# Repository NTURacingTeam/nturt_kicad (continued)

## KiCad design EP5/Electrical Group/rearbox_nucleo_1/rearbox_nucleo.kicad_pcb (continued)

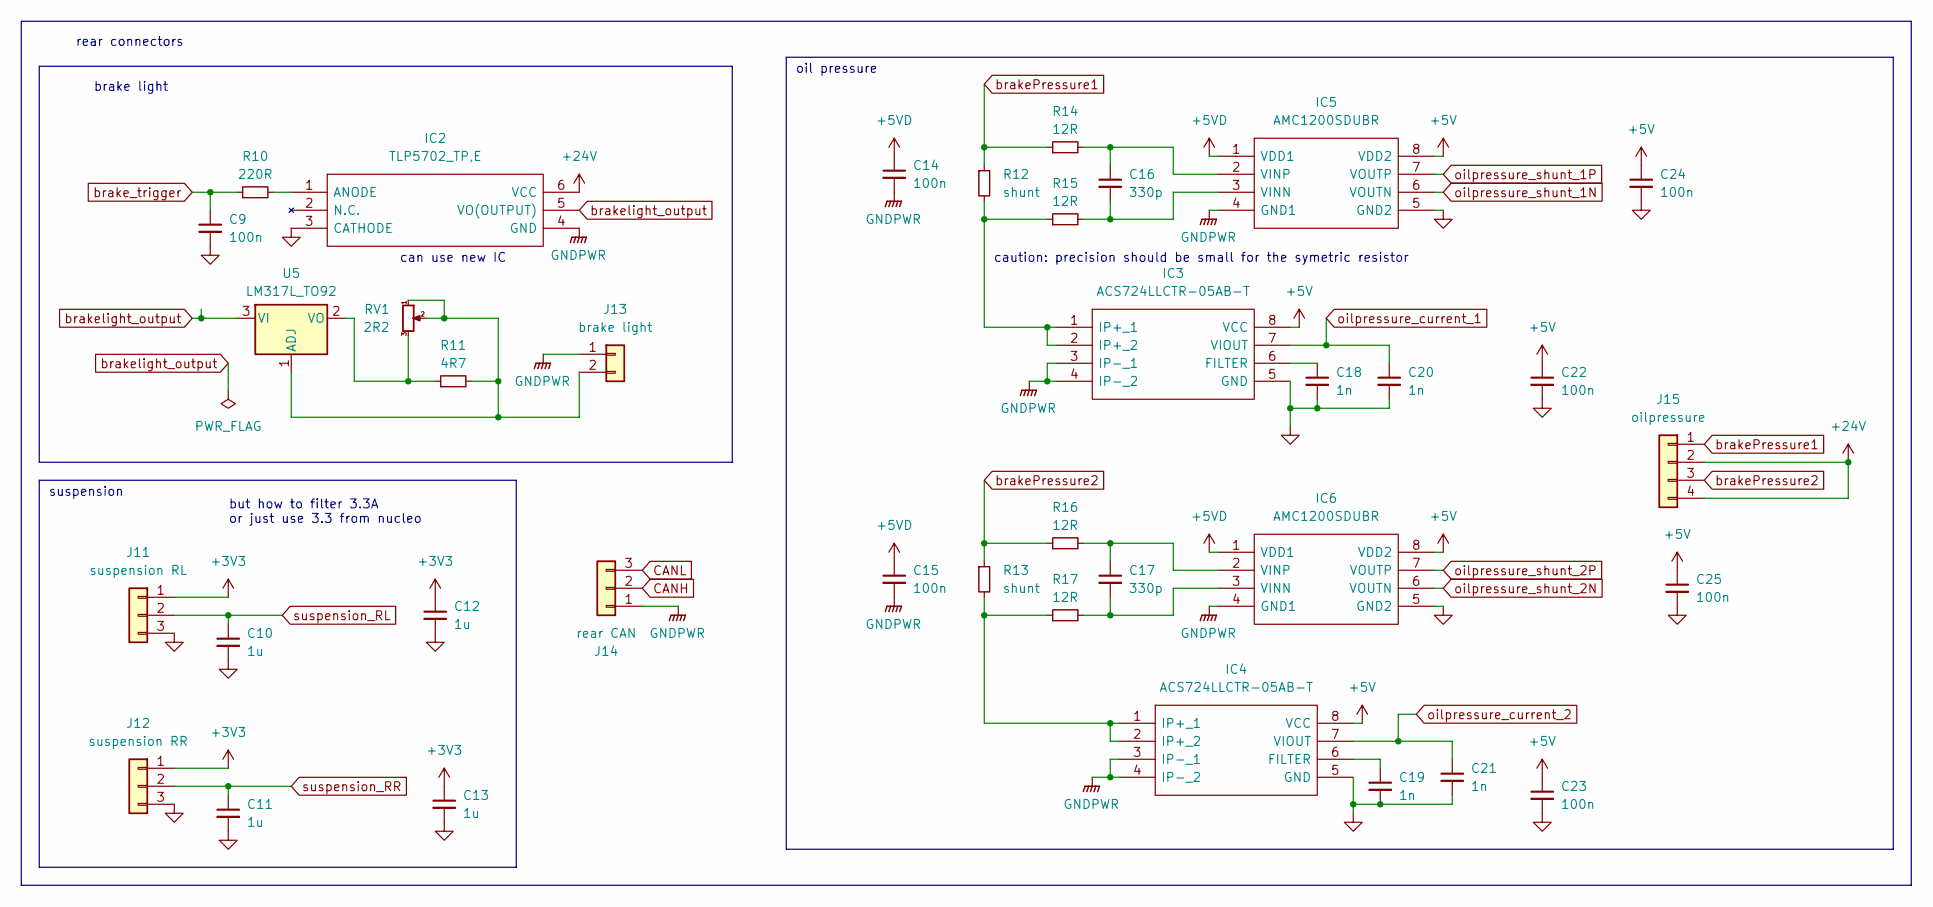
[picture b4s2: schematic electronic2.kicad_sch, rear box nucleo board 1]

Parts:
C9, C14, C15, C22, C23, C24, C25: 100n; C_0805_2012Metric
C10, C11, C12, C13: 1u; C_0805_2012Metric
C16, C17: 330p; C_0805_2012Metric
C18, C19, C20, C21: 1n; C_0805_2012Metric
IC2: TLP5702_TP,E; SOT127P1000X230-6N; Mouser Part Number 757-TLP5702(TPE
IC3, IC4: ACS724LLCTR-05AB-T; SOIC127P600X175-8N; Mouser Part Number 250-724LLCTR05ABT
IC5, IC6: AMC1200SDUBR; SOP254P1040X485-8N; Mouser Part Number 595-AMC1200SDUBR
J11: suspension RL; JST_XH_B3B-XH-A_1x03_P2.50mm_Vertical
J12: suspension RR; JST_XH_B3B-XH-A_1x03_P2.50mm_Vertical
J13: brake light; JST_XH_B2B-XH-A_1x02_P2.50mm_Vertical
J14: rear CAN; JST_XH_B3B-XH-A_1x03_P2.50mm_Vertical
J15: oilpressure; JST_XH_B4B-XH-A_1x04_P2.50mm_Vertical
R10: 220R; R_0805_2012Metric
R11: 4R7; R_Axial_DIN0516_L15.5mm_D5.0mm_P5.08mm_Vertical
R12, R13: shunt; R_0805_2012Metric
R14, R15, R16, R17: 12R; R_0805_2012Metric
RV1: 2R2; Potentiometer_Piher_T-16H_Single_Horizontal
U5: LM317L_TO92; TO-220-3_Vertical

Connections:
+3V3: C12.1, C13.1, J11.1, J12.1; also elsewhere on the board
+5V: C22.1, C23.1, C24.1, C25.1, IC3.8 (VCC), IC4.8 (VCC), IC5.8 (VDD2), IC6.8 (VDD2); also elsewhere on the board
+5VD: C14.1, C15.1, IC5.1 (VDD1), IC6.1 (VDD1); also elsewhere on the board
CANH: J14.2; also elsewhere on the board
CANL: J14.3; also elsewhere on the board
GND: C9.2, C10.2, C11.2, C12.2, C13.2, C18.2, C19.2, C20.2, C21.2, C22.2, C23.2, C24.2, C25.2, IC2.3 (CATHODE), IC3.5 (GND), IC4.5 (GND), IC5.5 (GND2), IC6.5 (GND2), J11.3, J12.3; also elsewhere on the board
GNDPWR: C14.2, C15.2, IC2.4 (GND), IC3.3 (IP-_1), IC3.4 (IP-_2), IC4.3 (IP-_1), IC4.4 (IP-_2), IC5.4 (GND1), IC6.4 (GND1), J13.1, J14.1; also elsewhere on the board
unnamed: IC2.1 (ANODE), R10.2
unnamed: C18.1, IC3.6 (FILTER)
unnamed: IC3.1 (IP+_1), IC3.2 (IP+_2), R12.2, R15.1
unnamed: C19.1, IC4.6 (FILTER)
unnamed: IC4.1 (IP+_1), IC4.2 (IP+_2), R13.2, R17.1
unnamed: C16.2, IC5.3 (VINN), R15.2
unnamed: C16.1, IC5.2 (VINP), R14.2
unnamed: C17.2, IC6.3 (VINN), R17.2
unnamed: C17.1, IC6.2 (VINP), R16.2
unnamed: J13.2, R11.2, RV1.1, RV1.2, U5.1 (ADJ)
unnamed: R11.1, RV1.3, U5.2 (VO)
brakePressure1: J15.1, R12.1, R14.1
brakePressure2: J15.3, R13.1, R16.1
brake_trigger: C9.1, R10.1; also elsewhere on the board
brakelight_output: IC2.5 (VO(OUTPUT)), U5.3 (VI)
oilpressure_current_1: C20.1, IC3.7 (VIOUT); also elsewhere on the board
oilpressure_current_2: C21.1, IC4.7 (VIOUT); also elsewhere on the board
oilpressure_shunt_1N: IC5.6 (VOUTN); also elsewhere on the board
oilpressure_shunt_1P: IC5.7 (VOUTP); also elsewhere on the board
oilpressure_shunt_2N: IC6.6 (VOUTN); also elsewhere on the board
oilpressure_shunt_2P: IC6.7 (VOUTP); also elsewhere on the board
suspension_RL: C10.1, J11.2; also elsewhere on the board
suspension_RR: C11.1, J12.2; also elsewhere on the board

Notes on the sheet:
can use new IC
oil pressure
but how to filter 3.3A or just use 3.3 from nucleo
caution: precision should be small for the symetric resistor
brake light
rear connectors
suspension

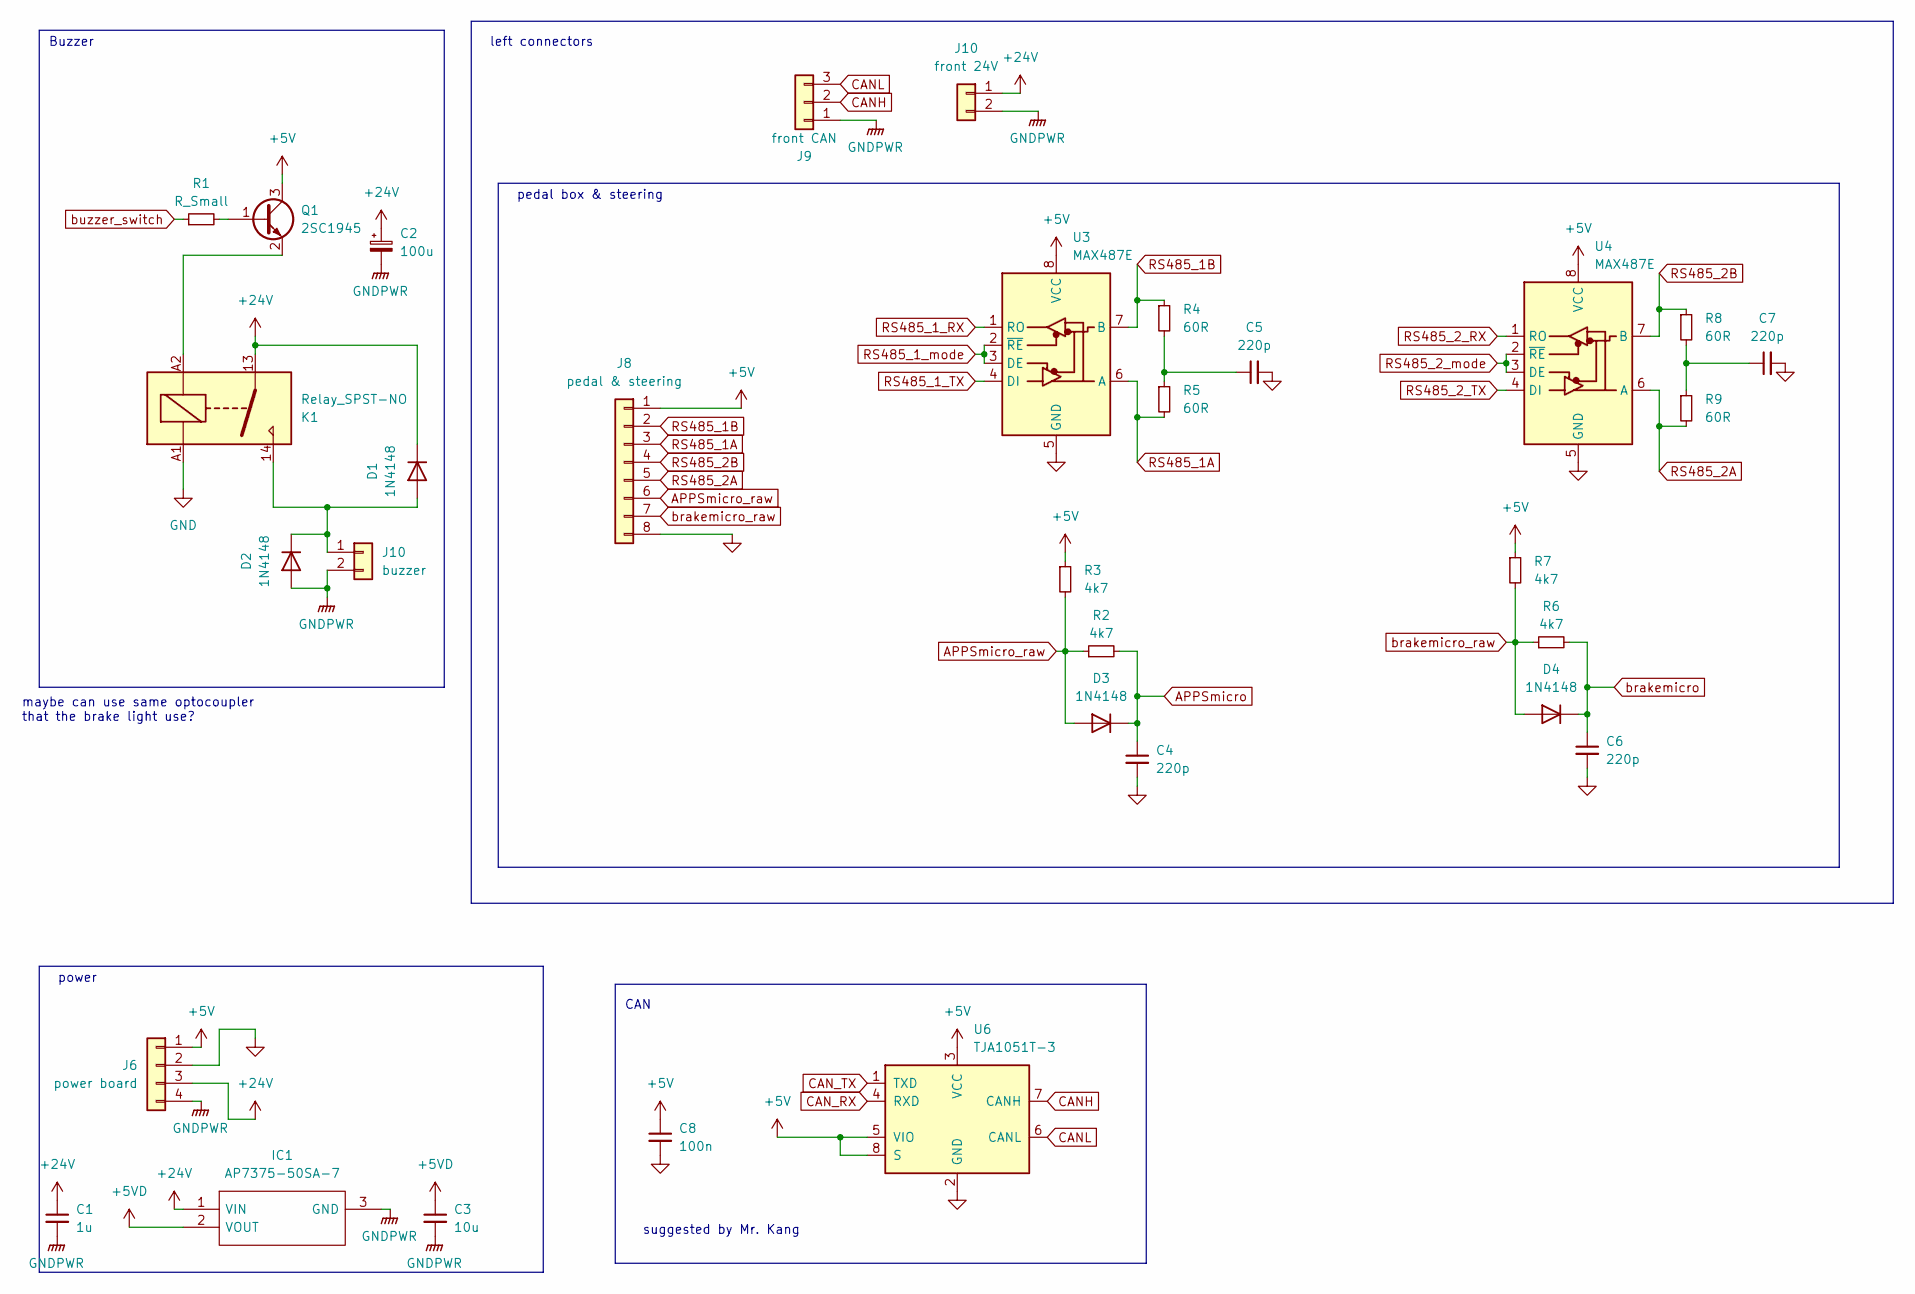
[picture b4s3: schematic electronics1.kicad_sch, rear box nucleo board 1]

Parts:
C1: 1u; C_0805_2012Metric
C2: 100u; C_Radial_D6.3mm_H11.0mm_P2.50mm
C3: 10u; C_0805_2012Metric
C4, C5, C6, C7: 220p; C_0805_2012Metric
C8: 100n; C_0805_2012Metric
D1, D2, D3, D4: 1N4148; D_MiniMELF
IC1: AP7375-50SA-7; SOT96P240X110-3N; Mouser Part Number 621-AP7375-50SA-7
J6: power board; JST_XH_B4B-XH-A_1x04_P2.50mm_Vertical
J8: pedal & steering; JST_XH_B8B-XH-A_1x08_P2.50mm_Vertical
J9: front CAN; JST_XH_B3B-XH-A_1x03_P2.50mm_Vertical
J10: buzzer; JST_XH_B2B-XH-A_1x02_P2.50mm_Vertical
K1: Relay_SPST-NO; Relay_SPST_Omron_G2RL-1A-E
Q1: 2SC1945; TO-220-3_Vertical
R1: R_Small; R_0805_2012Metric
R2, R3, R6, R7: 4k7; R_0805_2012Metric
R4, R5, R8, R9: 60R; R_0805_2012Metric
U3, U4: MAX487E; SOIC-8_3.9x4.9mm_P1.27mm
U6: TJA1051T-3; SOIC-8_3.9x4.9mm_P1.27mm

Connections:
+5V: C8.1, J6.1, J8.1, Q1.3 (C), R3.1, R7.1, U3.8 (VCC), U4.8 (VCC); also elsewhere on the board
+5VD: C3.1, IC1.2 (VOUT); also elsewhere on the board
APPSmicro: C4.1, D3.1 (K), R2.2; also elsewhere on the board
APPSmicro_raw: D3.2 (A), J8.6, R2.1, R3.2
CANH: J9.2; also elsewhere on the board
CANL: J9.3; also elsewhere on the board
GND: C4.2, C5.2, C6.2, C7.2, C8.2, J6.2, J8.8, K1.A1, U3.5 (GND), U4.5 (GND); also elsewhere on the board
GNDPWR: C1.2, C2.2, C3.2, D2.2 (A), IC1.3 (GND), J6.4, J9.1, J10.2; also elsewhere on the board
unnamed: C5.1, R4.2, R5.1
unnamed: C7.1, R8.2, R9.1
unnamed: Q1.1 (B), R1.2
unnamed: K1.A2, Q1.2 (E)
RS485_1A: J8.3, R5.2, U3.6 (A)
RS485_1B: J8.2, R4.1, U3.7 (B)
RS485_1_RX: U3.1 (RO); also elsewhere on the board
RS485_1_TX: U3.4 (DI); also elsewhere on the board
RS485_1_mode: U3.2 (~RE), U3.3 (DE); also elsewhere on the board
RS485_2A: J8.5, R9.2, U4.6 (A)
RS485_2B: J8.4, R8.1, U4.7 (B)
RS485_2_RX: U4.1 (RO); also elsewhere on the board
RS485_2_TX: U4.4 (DI); also elsewhere on the board
RS485_2_mode: U4.2 (~RE), U4.3 (DE); also elsewhere on the board
brakemicro: C6.1, D4.1 (K), R6.2; also elsewhere on the board
brakemicro_raw: D4.2 (A), J8.7, R6.1, R7.2
buzzer_switch: R1.1; also elsewhere on the board

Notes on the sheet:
Buzzer
maybe can use same optocoupler that the brake light use?
power
pedal box & steering
suggested by Mr. Kang
CAN
left connectors

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
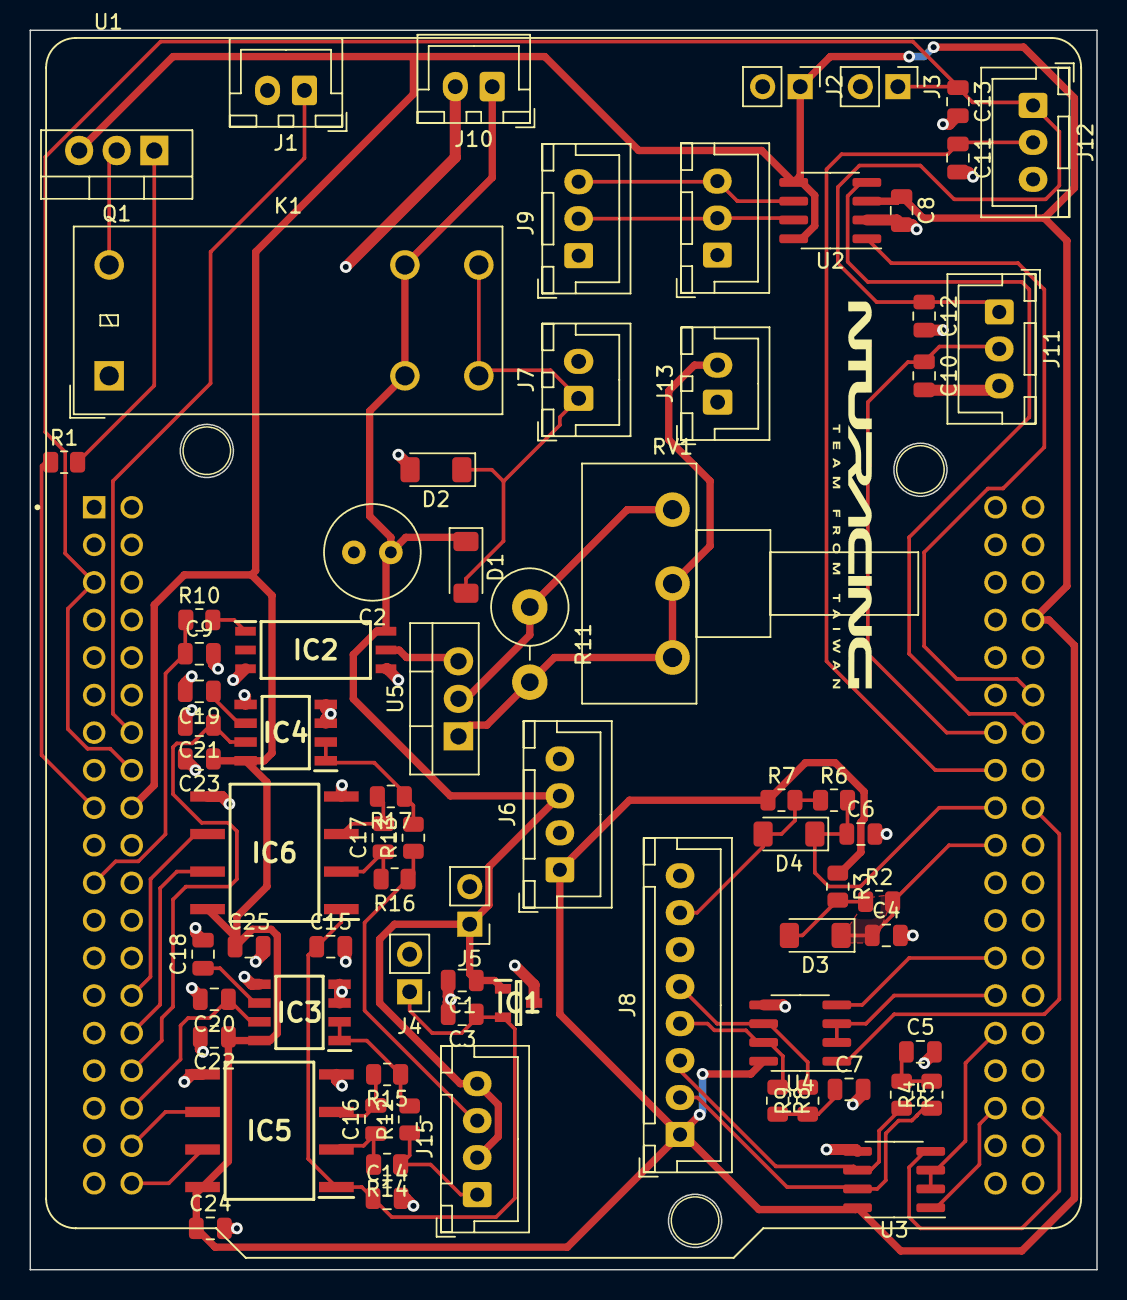
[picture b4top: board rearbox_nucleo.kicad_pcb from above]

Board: 2 copper layers, 72.1 x 83.8 mm, 75 parts (0 on the bottom side), 54 nets.

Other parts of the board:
J7: buzzer; JST_XH_B2B-XH-A_1x02_P2.50mm_Vertical
U2: TJA1051T-3; SOIC-8_3.9x4.9mm_P1.27mm

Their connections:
+5V: U2.3 (VCC), U2.5 (VIO), U2.8 (S); also elsewhere on the board
CANH: U2.7 (CANH); also elsewhere on the board
CANL: U2.6 (CANL); also elsewhere on the board
CAN_RX: U2.4 (RXD); also elsewhere on the board
CAN_TX: U2.1 (TXD); also elsewhere on the board
GND: U2.2 (GND); also elsewhere on the board
GNDPWR: J7.2; also elsewhere on the board

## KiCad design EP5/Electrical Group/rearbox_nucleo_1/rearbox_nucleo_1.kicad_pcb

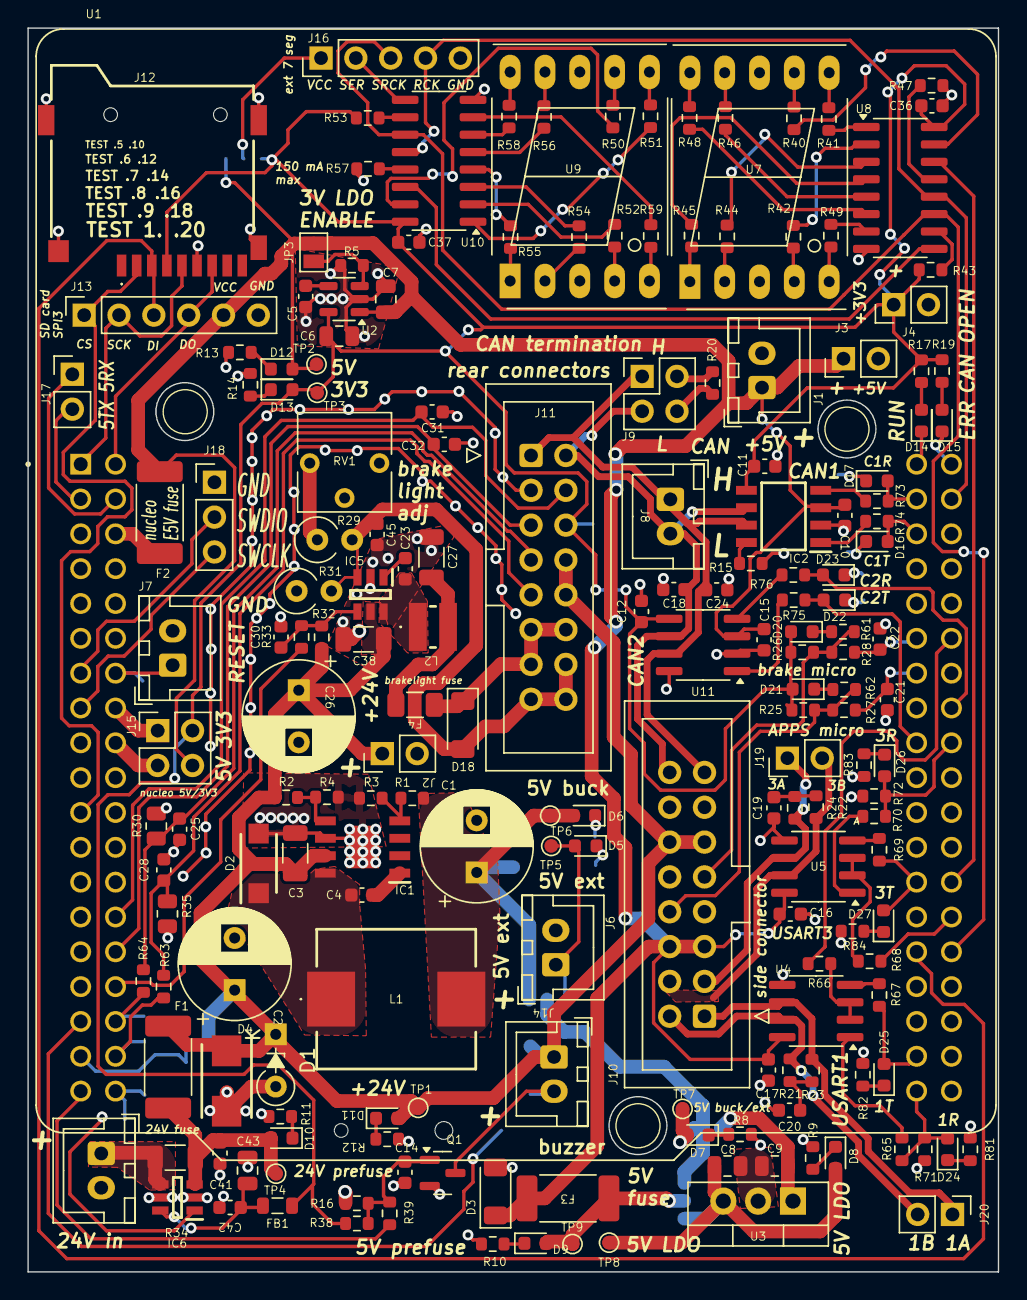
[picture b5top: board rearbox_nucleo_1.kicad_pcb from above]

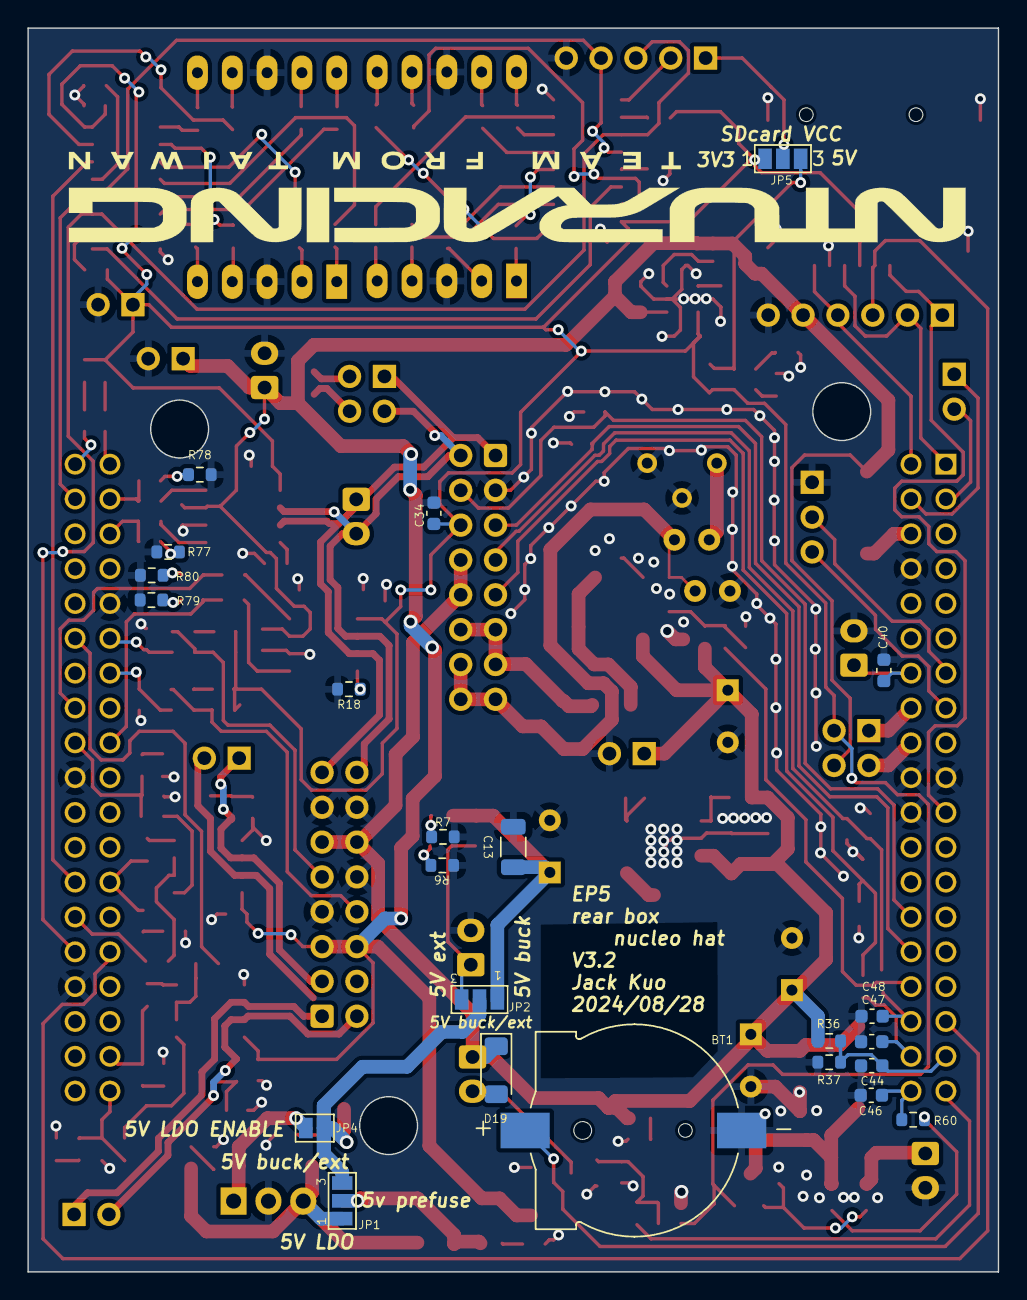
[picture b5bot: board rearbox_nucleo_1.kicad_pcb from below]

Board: 2 copper layers, 70.8 x 90.7 mm, 213 parts (23 on the bottom side), 153 nets.

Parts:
BT1: 1056; BAT_1056
C1: 470u 16V; CP_Radial_D8.0mm_P3.80mm
C2, C26: 220u 35V; CP_Radial_D8.0mm_P3.80mm
C3, C38: 10u 35V; C_1206_3216Metric
C4, C5, C41: 10n; C_0603_1608Metric
C6, C7, C8, C9, C43: 10u 16V; C_0805_2012Metric
C10, C11, C12, C14, C15, C16, C17, C21, C22, C23, C30, C36, C37, C40, C42, C45, C47, C48: 0u1; C_0603_1608Metric
C13, C27: 22u 16V; C_1206_3216Metric
C18, C24, C25, C28: 330p; C_0603_1608Metric
C19, C20: 220p; C_0603_1608Metric
C31, C32, C44: 1u 16V; C_0603_1608Metric
C34: 10u 16V; C_0603_1608Metric
C46: 10u; C_0603_1608Metric
D1: zener 27V; D_DO-35_SOD27_P3.81mm_Vertical_KathodeUp_Zener
D2: 45V 5A (VSSAF5L45HM3_A_H); SODFL5226X100N
D3: zener 5.6V; D_MiniMELF
D4: SMBJP6KE33A-TP; DIOM5336X262N
D5, D9: RED 5Vext; LED_0603_1608Metric
D6: RED 5Vbuck; LED_0603_1608Metric
D7: RED 5Vbuck/ext; LED_0603_1608Metric
D8: RED 5Vldo; LED_0603_1608Metric
D10: RED 24VpreFuse; LED_0603_1608Metric
D11: RED 24V; LED_0603_1608Metric
D12: RED 5V; LED_0603_1608Metric
D13: RED 3V3; LED_0603_1608Metric
D14: GREEN CANopen_RUN; LED_0603_1608Metric
D15: RED CANopen_ERR; LED_0603_1608Metric
D16: BLUE CAN1_TX; LED_0603_1608Metric
D17: BLUE CAN1_RX; LED_0603_1608Metric
D18, D19: 1N4148; D_MiniMELF
D20: ORANGE brake micro; LED_0603_1608Metric
D21: WHITE APPS micro; LED_0603_1608Metric
D22: BLUE CAN2_TX; LED_0603_1608Metric
D23: BLUE CAN2_RX; LED_0603_1608Metric
D24: WHITE USART1_RX; LED_0603_1608Metric
D25: WHITE USART1_TX; LED_0603_1608Metric
D26: WHITE USART3_RX; LED_0603_1608Metric
D27: WHITE USART3_TX; LED_0603_1608Metric
F1: 2A; Fuse_2512_6332Metric_Pad1.52x3.35mm_HandSolder
F2: 0.4A; Fuse_2512_6332Metric_Pad1.52x3.35mm_HandSolder
F3: 1A; Fuse_2512_6332Metric_Pad1.52x3.35mm_HandSolder
F4: 0.5A; Fuse_1206_3216Metric
FB1: FerriteBead; L_0805_2012Metric
IC1: LM22676MRX-ADJ_NOPB; SOIC127P600X170-9N
IC2: TCAN1057AVDRQ1; SOIC127P600X175-8N
IC5: LMR50410Y3FQDBVRQ1; SOT95P280X145-6N
IC6: MCP6C04T-100E_CHY; SOT95P280X145-6N
J1: 5Vout; JST_XH_B2B-XH-A_1x02_P2.50mm_Vertical
J2: 24V test; PinHeader_1x02_P2.54mm_Vertical
J3: 5V test; PinHeader_1x02_P2.54mm_Vertical
J4: 3V3 test; PinHeader_1x02_P2.54mm_Vertical
J5: 24V; JST_XH_B2B-XH-A_1x02_P2.50mm_Vertical
J6: 5V external; JST_XH_B2B-XH-A_1x02_P2.50mm_Vertical
J7: RESET; JST_XH_B2B-XH-A_1x02_P2.50mm_Vertical
J8: CAN; JST_XH_B2B-XH-A_1x02_P2.50mm_Vertical
J9: CAN_termination; PinHeader_2x02_P2.54mm_Vertical
J10: left connector; IDC-Header_2x08_P2.54mm_Vertical
J11: rear_connector; IDC-Header_2x08_P2.54mm_Vertical
J12: MSD-4-A; MSD4A
J13: sdCardModule; PinSocket_1x06_P2.54mm_Vertical
J14: buzzer; JST_XH_B2B-XH-A_1x02_P2.50mm_Vertical
J15: nucleoPWRjumper; PinHeader_2x02_P2.54mm_Vertical
J16: 7 seg module; PinHeader_1x05_P2.54mm_Vertical
J17: UART5; PinHeader_1x02_P2.54mm_Vertical
J18: SW debug; PinHeader_1x03_P2.54mm_Vertical
J19: RS485_3; PinHeader_1x02_P2.54mm_Vertical
J20: RS485_1; PinHeader_1x02_P2.54mm_Vertical
JP1: 5Vprefuse; SolderJumper-3_P1.3mm_Open_Pad1.0x1.5mm_NumberLabels
JP2: 5VonBoard; SolderJumper-3_P1.3mm_Open_Pad1.0x1.5mm_NumberLabels
JP3: 3.3ON; SolderJumper-2_P1.3mm_Open_Pad1.0x1.5mm
JP4: 5V_LDO; SolderJumper-2_P1.3mm_Open_Pad1.0x1.5mm
JP5: seg pwr; SolderJumper-3_P1.3mm_Open_Pad1.0x1.5mm_NumberLabels
L1: 47u 3A (AMRM00101040470MA1); AMRM00101040470MA1
L2: 10uH 2A (SRN3012BTA-100M); SRN3012BTA100M
Q1: BSS138; SOT-23
R1, R36: 27k; R_0603_1608Metric
R2: 4.7k; R_0603_1608Metric
R3: 9k1; R_0603_1608Metric
R4, R6, R7, R8, R9, R10, R13, R16, R33, R38, R43, R47, R53, R57, R65, R66, R67, R68, R69, R70, R77, R78, R79, R80, R81, R82, R83, R84: 1k; R_0603_1608Metric
R5, R32, R39, R60: 100k; R_0603_1608Metric
R11, R12, R15, R18, R25, R26, R63, R64: 10k; R_0603_1608Metric
R14, R27, R28, R61, R62, R73, R74, R75, R76: 510R; R_0603_1608Metric
R17, R19, R40, R41, R42, R44, R45, R46, R48, R49, R50, R51, R52, R54, R55, R56, R58, R59: 150R; R_0603_1608Metric
R20: 120R; R_0603_1608Metric
R21, R22, R23, R24: 60R; R_0603_1608Metric
R29, R31: 5.1R 1/2W; R_Axial_DIN0309_L9.0mm_D3.2mm_P2.54mm_Vertical
R30, R35: 100R 1%; R_0805_2012Metric
R34: 10mR shunt; R_1206_3216Metric
R37: 3k; R_0603_1608Metric
R71, R72: 2k2; R_0603_1608Metric
RV1: 20k; Potentiometer_Vishay_T73YP_Vertical
TP1: 24V; TestPoint_Pad_D1.0mm
TP2: 5V; TestPoint_Pad_D1.0mm
TP3: 3V3; TestPoint_Pad_D1.0mm
TP4: 24V_prefuse; TestPoint_Pad_D1.0mm
TP5: 5v_ext; TestPoint_Pad_D1.0mm
TP6: 5V_buck; TestPoint_Pad_D1.0mm
TP7: 5V_onboard/ext; TestPoint_Pad_D1.0mm
TP8: 5V_LDO; TestPoint_Pad_D1.0mm
TP9: 5V_prefuse; TestPoint_Pad_D1.0mm
U1: NUCLEO-G474RE; MODULE_NUCLEO-G474RE
U2: LP2985-3.3; SOT-23-5
U3: LM7805_TO220; TO-220-3_Vertical
U4, U5: MAX487E; SOIC-8_3.9x4.9mm_P1.27mm
U7, U9: SM420561N; 7SegmentLED_LTS6760_LTS6780
U8, U10: 74HC595; SOIC-16_3.9x9.9mm_P1.27mm
U11: TJA1051T-3; SOIC-8_3.9x4.9mm_P1.27mm

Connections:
5V_nucleo_E5V: F2.2, U1.CN7_6 (E5V)
24Vcurrent: IC6.1 (VOUT), R60.2
24Vvoltage: C44.1, R36.2, R37.1, U1.CN7_35 (PC2)
+3V3: C6.1, C11.1, C12.1, C34.1, C36.1, C37.1, D13.2 (A), D20.2 (A), D21.2 (A), FB1.1, IC2.5 (NCVIO), J4.1, J11.6, J12.4 (VDD), J15.2, JP5.1 (A), R17.1, R19.1, R25.1, R26.1, R38.2, R43.1, R53.1, TP3.1, U2.5 (VOUT), U8.16 (VCC), U10.16 (VCC), U11.5 (VIO)
+5V: C7.1, C10.1, C15.1, C16.1, C17.1, D3.1 (K), D12.2 (A), F2.1, F3.2, IC2.3 (VCC), J1.1, J3.1, J10.5, J10.6, J13.5, J15.4, JP3.2 (B), JP5.3 (B), TP2.1, U2.1 (VIN), U4.8 (VCC), U5.8 (VCC), U11.3 (VCC)
+24V: C2.1, C3.1, C26.1, C38.1, D1.1 (K), D4.1 (K), D11.2 (A), D19.1 (K), F1.2, IC1.7 (VIN), IC5.5 (VIN), J2.1, J10.11, J10.12, J11.8, J11.10, J14.1, R2.1, R32.1, R36.1, TP1.1
/3V_nucleo: J15.1, U1.CN7_16 (+3V3)
/5V_nucleo: J15.3, U1.CN7_18 (+5V)
/RESET: C40.1, J7.1, U1.CN7_14 (~RST)
/T_SWCLK: J18.3, U1.CN7_15 (PA14)
/T_SWDIO: J18.2, U1.CN7_13 (PA13)
/electronic2/BL_SW: C23.1, IC5.6 (SW), L2.1
/electronic2/VCC_brakelightprefuse: C27.1, F4.2, L2.2
/electronic3/buzzer_outbox: D19.2 (A), J14.2, Q1.3 (D)
/power/5V_LDO: C8.1, D8.2 (A), JP1.1 (A), TP8.1, U3.3 (VO)
/power/5V_buck: C1.1, C13.1, D6.2 (A), JP2.1 (A), L1.2, R1.1, TP6.1
/power/5V_buck_EN: IC1.5 (EN), R2.2, R4.1
/power/5V_buck_FB: IC1.4 (FB), R1.2, R3.1
/power/5V_buck_sw: C4.1, D2.1 (K), IC1.8 (SW), L1.1
/power/5V_buck/ext: D7.2 (A), JP1.3 (B), JP2.2 (C), JP4.1 (A), TP7.1
/power/5V_ext: D5.2 (A), J6.1, JP2.3 (B), TP5.1
/power/5V_prefuse: D9.2 (A), F3.1, JP1.2 (C), TP9.1
/power/24V_prefuse: C41.1, D10.2 (A), F1.1, IC6.3 (VIP), R34.2, TP4.1
/power/24V_premeasure: IC6.4 (VIM), J5.1, R34.1
APPSmicro: C21.1, R27.1, U1.CN10_13 (PA6)
APPSmicro_raw: J10.8, R25.2, R27.2, R62.2
CANH: C24.1, IC2.7 (CANH), J8.1, J9.1, J10.15, J11.1, U11.7 (CANH)
CANL: C18.1, IC2.6 (CANL), J8.2, J9.3, J10.16, J11.2, U11.6 (CANL)
CANOPEN_ERR_LED: D15.1 (K), U1.CN10_2 (PC8)
CANOPEN_RUN_LED: D14.1 (K), U1.CN10_1 (PC9)
FDCAN1_RX: D17.2 (A), R73.1, U1.CN10_3 (PB8)
FDCAN1_TX: D16.2 (A), R74.1, U1.CN10_5 (PB9)
FDCAN2_RX: D23.2 (A), R76.1, U1.CN10_16 (PB12)
FDCAN2_TX: D22.2 (A), R75.1, U1.CN10_17 (PB6)
GND: BT1.N, C1.2, C2.2, C3.2, C5.2, C6.2, C7.2, C8.2, C9.2, C10.2, C11.2, C12.2, C13.2, C14.2, C15.2, C16.2, C17.2, C18.2, C19.2, C20.2, C21.2, C22.2, C24.2, C25.2, C26.2, C27.2, C28.2, C30.2, C31.2, C32.2, C34.2, C36.2, C37.2, C38.2, C40.2, C41.2, C42.2, C43.2, C44.2, C45.2, C46.2, C47.2, C48.2, D1.2 (A), D2.2 (A), D3.2 (A), D4.2 (A), IC1.6 (GND_1), IC1.9 (GND_2), IC2.2 (GND), IC5.2 (GND), IC6.2 (VSS), IC6.5 (VREF), J1.2, J2.2, J3.2, J4.2, J5.2, J6.2, J7.2, J10.7, J10.10, J10.13, J10.14, J11.3, J12.6 (VSS), J12.G1 (GND_1), J12.G2 (GND_2), J12.G3 (GND_3), J12.G4 (GND_4), J13.6, J16.5, J18.1, Q1.2 (S), R3.2, R4.2, R5.2, R6.2, R7.2, R8.2, R9.2, R10.2, R11.2, R12.2, R13.2, R14.2, R15.1, R16.1, R18.1, R30.2, R31.1, R35.2, R37.2, R47.1, R57.1, R71.2, R72.2, R77.2, R78.2, R79.2, R80.2, R81.1, R82.1, R83.1, R84.1, RV1.2, RV1.3, U1.CN7_8 (GND_CN7_8), U1.CN7_19 (GND_CN7_19), U1.CN7_20 (GND_CN7_20), U1.CN7_22 (GND_CN7_22), U1.CN10_9 (GND_CN10_9), U1.CN10_20 (GND_CN10_20), U1.CN10_32 (AGND), U2.2 (GND), U3.2 (GND), U4.5 (GND), U5.5 (GND), U7.3 (CC), U7.8 (CC), U8.8 (GND), U9.3 (CC), U9.8 (CC), U10.8 (GND), U11.2 (GND)
unnamed: C19.1, R22.2, R24.1
unnamed: C20.1, R21.2, R23.1
unnamed: D5.1 (K), R6.1
unnamed: D6.1 (K), R7.1
unnamed: D7.1 (K), R8.1
unnamed: D8.1 (K), R9.1
unnamed: D9.1 (K), R10.1
unnamed: D10.1 (K), R11.1
unnamed: D11.1 (K), R12.1
unnamed: D12.1 (K), R13.1
unnamed: D13.1 (K), R14.1
unnamed: D14.2 (A), R17.2
unnamed: D15.2 (A), R19.2
unnamed: D16.1 (K), R77.1
unnamed: D17.1 (K), R78.1
unnamed: D20.1 (K), R61.1
unnamed: D21.1 (K), R62.1
unnamed: D22.1 (K), R79.1
unnamed: D23.1 (K), R80.1
unnamed: D24.1 (K), R81.2
unnamed: D25.1 (K), R82.2
unnamed: D26.1 (K), R83.2
unnamed: D27.1 (K), R84.2
unnamed: C4.2, IC1.1 (BOOT)
unnamed: IC2.4 (RXD), R73.2
unnamed: IC2.8 (S), R15.2
unnamed: IC2.1 (TXD), R74.2
unnamed: C23.2, IC5.1 (CB)
unnamed: C30.1, IC5.4 (EN), R32.2, R33.1
unnamed: J9.2, R20.2
unnamed: J9.4, R20.1
unnamed: J16.1, JP5.2 (C)
unnamed: J16.2, U10.9 (QH')
unnamed: JP3.1 (A), R5.1, U2.3 (ON/~OFF)
unnamed: C9.1, JP4.2 (B), U3.1 (VI)
unnamed: C14.1, Q1.1 (G), R16.2, R38.1, R39.1
unnamed: R29.1, RV1.1
unnamed: C48.1, R64.1, U1.CN7_34 (PB0)
unnamed: C46.1, R60.1, U1.CN7_38 (PC0/PA15)
unnamed: C47.1, R63.1, U1.CN7_36 (PC1/PB9)
unnamed: C5.1, U2.4 (BP)
unnamed: R66.1, U4.2 (~RE), U4.3 (DE)
unnamed: R67.1, U4.4 (DI)
unnamed: R65.1, U4.1 (RO)
unnamed: R68.1, U5.2 (~RE), U5.3 (DE)
unnamed: R69.1, U5.4 (DI)
unnamed: R70.1, U5.1 (RO)
unnamed: R40.2, U7.7 (A)
unnamed: R41.2, U7.6 (B)
unnamed: R42.2, U7.4 (C)
unnamed: R44.2, U7.2 (D)
unnamed: R49.2, U7.5 (DP)
unnamed: R45.2, U7.1 (E)
unnamed: R46.2, U7.9 (F)
unnamed: R48.2, U7.10 (G)
unnamed: R40.1, U8.15 (QA)
unnamed: R41.1, U8.1 (QB)
unnamed: R42.1, U8.2 (QC)
unnamed: R44.1, U8.3 (QD)
unnamed: R45.1, U8.4 (QE)
unnamed: R46.1, U8.5 (QF)
unnamed: R48.1, U8.6 (QG)
unnamed: R49.1, U8.7 (QH)
unnamed: R47.2, U8.13 (~OE)
unnamed: R43.2, U8.10 (~SRCLR)
unnamed: R50.2, U9.7 (A)
unnamed: R51.2, U9.6 (B)
unnamed: R52.2, U9.4 (C)
unnamed: R54.2, U9.2 (D)
unnamed: R59.2, U9.5 (DP)
unnamed: R55.2, U9.1 (E)
unnamed: R56.2, U9.9 (F)
unnamed: R58.2, U9.10 (G)
unnamed: R50.1, U10.15 (QA)
unnamed: R51.1, U10.1 (QB)
unnamed: R52.1, U10.2 (QC)
unnamed: R54.1, U10.3 (QD)
unnamed: R55.1, U10.4 (QE)
unnamed: R56.1, U10.5 (QF)
unnamed: R58.1, U10.6 (QG)
unnamed: R59.1, U10.7 (QH)
unnamed: U8.9 (QH'), U10.14 (SER)
unnamed: R57.2, U10.13 (~OE)
unnamed: R53.2, U10.10 (~SRCLR)
unnamed: R76.2, U11.4 (RXD)
unnamed: R18.2, U11.8 (S)
unnamed: R75.2, U11.1 (TXD)
SPI2_CS: J16.4, U1.CN10_4 (PC6), U8.12 (RCLK), U10.12 (RCLK)
SPI2_MOSI: U1.CN10_26 (PB15), U8.14 (SER)
SPI2_SCK: J16.3, U1.CN10_30 (PB13), U8.11 (SRCLK), U10.11 (SRCLK)
SPI3_CS: J12.2 (CD/DAT3), J13.1, U1.CN7_21 (PB7)
SPI3_MISO: J12.7 (DAT0), J13.4, U1.CN7_2 (PC11)
SPI3_MOSI: J12.3 (CMD), J13.3, U1.CN10_29 (PB5)
SPI3_SCK: J12.5 (CLK), J13.2, U1.CN7_1 (PC10)
UART5_RX: J17.1, U1.CN7_4 (PD2)
UART5_TX: J17.2, U1.CN7_3 (PC12)
USART1A: J10.1, J20.1, R23.2, U4.6 (A)
USART1B: J10.2, J20.2, R21.1, U4.7 (B)
USART1_DE: R66.2, U1.CN10_12 (PA12)
USART1_RX: D24.2 (A), R65.2, R71.1, U1.CN10_37 (PA3/PC5)
USART1_TX: D25.2 (A), R67.2, U1.CN10_35 (PA2/PC4)
USART3A: J10.3, J19.1, R24.2, U5.6 (A)
USART3B: J10.4, J19.2, R22.1, U5.7 (B)
USART3_DE: R68.2, U1.CN10_28 (PB14)
USART3_RX: D26.2 (A), R70.2, R72.1, U1.CN10_18 (PB11)
USART3_TX: D27.2 (A), R69.2, U1.CN10_25 (PB10)
VBAT: BT1.P, U1.CN7_33 (VBAT)
VDDA: C42.1, C43.1, FB1.2, IC6.6 (VDD)
brake_gate: R33.2, U1.CN7_32 (PA4)
brakelight_outboxN: C45.1, D18.2 (A), IC5.3 (FB), J11.14, J11.15, J11.16, R29.2, R31.2
brakelight_outboxP: D18.1 (K), F4.1, J11.11, J11.12, J11.13
brakemicro: C22.1, R28.1, U1.CN10_11 (PA5)
brakemicro_raw: J10.9, R26.2, R28.2, R61.2
buzzer_gate: R39.2, U1.CN7_37 (PC3)
oilpressure_shunt_1: C25.1, J11.7, R30.1, R64.2
oilpressure_shunt_2: C28.1, J11.9, R35.1, R63.2
suspension_R1: C31.1, J11.4, U1.CN7_28 (PA0)
suspension_R2: C32.1, J11.5, U1.CN7_30 (PA1)

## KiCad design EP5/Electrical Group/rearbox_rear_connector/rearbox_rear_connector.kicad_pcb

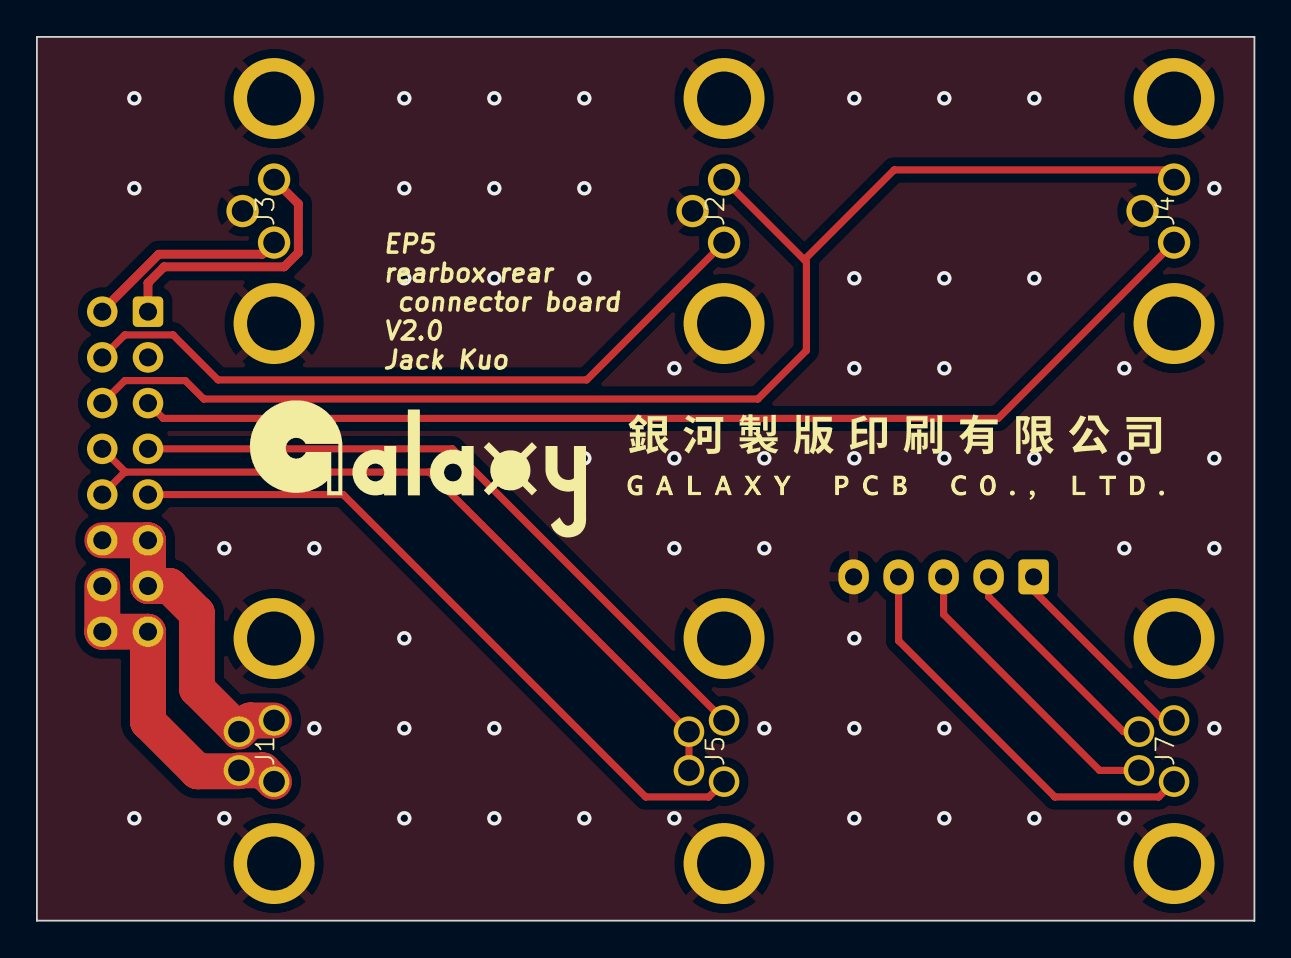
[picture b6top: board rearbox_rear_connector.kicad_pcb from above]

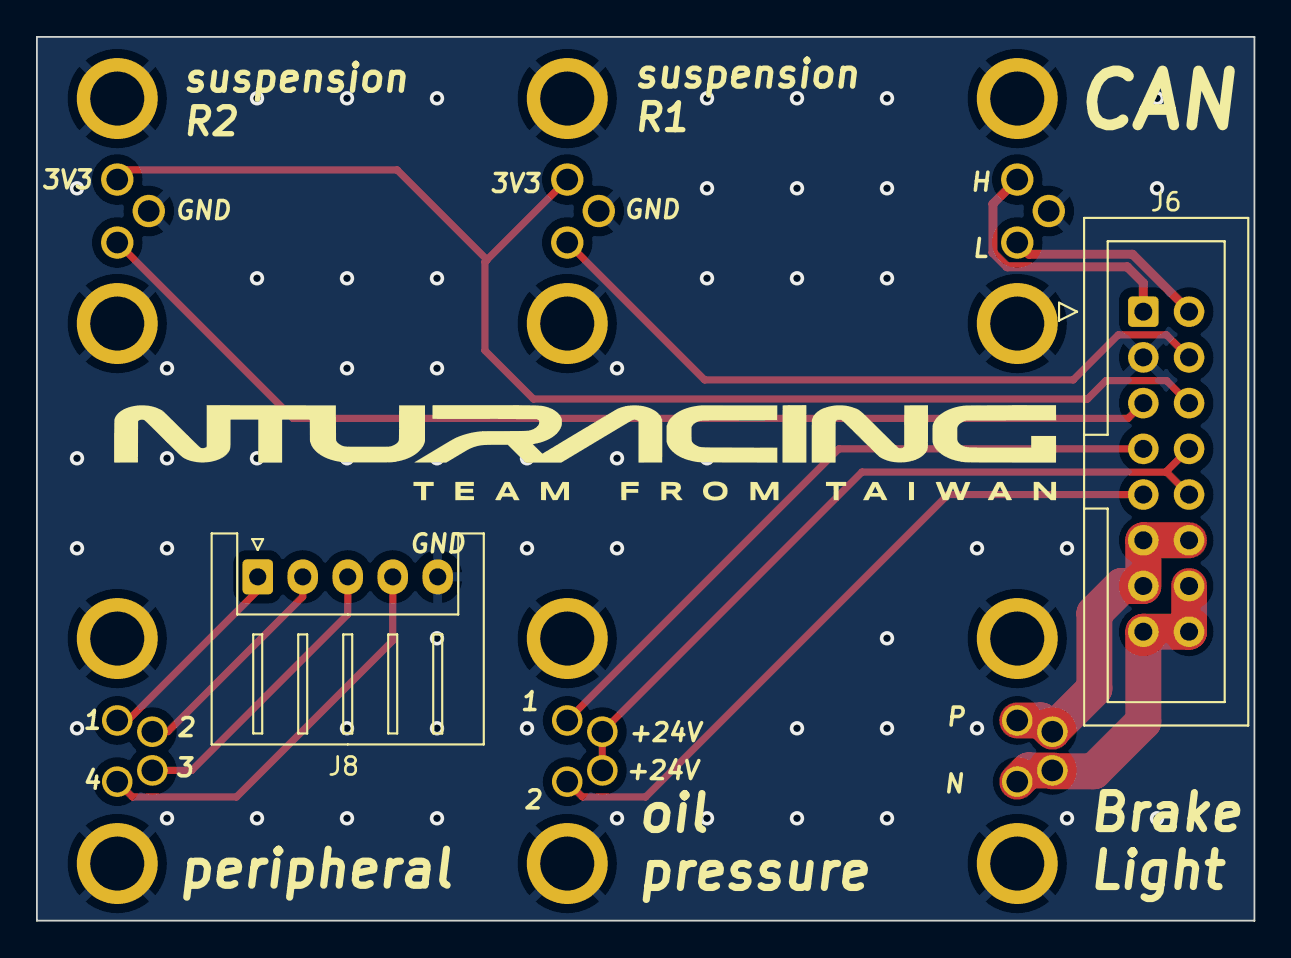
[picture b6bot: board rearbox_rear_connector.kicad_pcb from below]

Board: 2 copper layers, 67.6 x 49.1 mm, 8 parts (2 on the bottom side), 15 nets.

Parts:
J1: brake light; WP-04F3-26-11
J2: suspension RL; WP-03F3-09-11
J3: CAN; WP-03F3-09-11
J4: suspension RR; WP-03F3-09-11
J5: oil pressure; WP-04F3-26-11
J6: nucleo; IDC-Header_2x08_P2.54mm_Vertical
J7: peripheral; WP-04F3-26-11
J8: peripheral; JST_XH_S5B-XH-A_1x05_P2.50mm_Horizontal

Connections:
+3V3: J2.1, J4.1, J6.6
+24V: J5.2, J5.3, J6.8, J6.10
CANH: J3.1, J6.1
CANL: J3.3, J6.2
GND: J1.5, J2.4, J2.5, J3.4, J3.5, J4.4, J4.5, J5.5, J6.3, J7.5, J8.5
unnamed: J7.1, J8.1
unnamed: J7.2, J8.2
unnamed: J7.3, J8.3
unnamed: J7.4, J8.4
brakelight_outboxN: J1.3, J1.4, J6.14, J6.15, J6.16
brakelight_outboxP: J1.1, J1.2, J6.11, J6.12, J6.13
oilpressure_shunt_1: J5.1, J6.7
oilpressure_shunt_2: J5.4, J6.9
suspension_R1: J2.3, J6.4
suspension_R2: J4.3, J6.5

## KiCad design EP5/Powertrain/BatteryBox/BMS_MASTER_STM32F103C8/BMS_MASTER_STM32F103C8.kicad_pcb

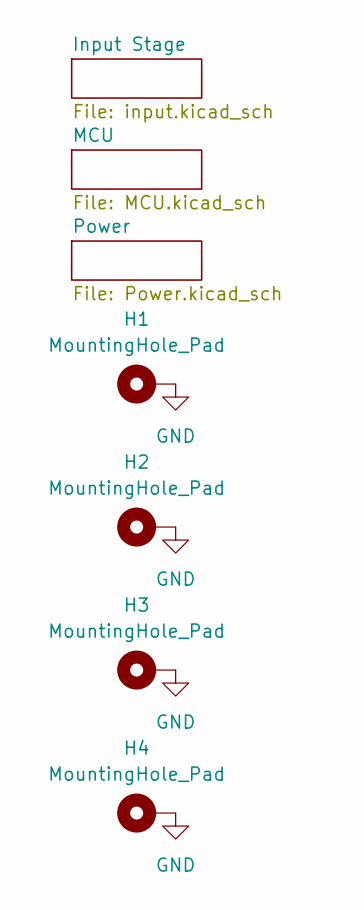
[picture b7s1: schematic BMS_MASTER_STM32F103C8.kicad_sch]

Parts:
H1, H2, H3, H4: MountingHole_Pad; MountingHole_4.3mm_M4_DIN965_Pad_TopBottom

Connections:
GND: H1.1, H2.1, H3.1, H4.1; also elsewhere on the board
